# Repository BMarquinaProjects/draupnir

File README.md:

# Draupnir

Analizador lógico de 8 canales: una Raspberry Pi Pico con el firmware libre [sigrok-pico](https://github.com/pico-coder/sigrok-pico) y PulseView en el PC, sobre una PCB propia con protección de entradas. **La v1 es solo para señales de 3,3 V.** El buffer que acepta 5 V (74LVC245) llega en la v2.

**EDA:** KiCad 10, con la biblioteca Forja de [Akmon](https://github.com/BMarquinaProjects/akmon)

<!-- Foto de la placa montada: fotos/draupnir.jpg (5 dic) -->

## Especificación

| | v1 |
|---|---|
| Canales | 8: D2 a D9 de sigrok-pico (GPIO 2 a 9 de la Pico) |
| Niveles de entrada | 3,3 V. **No admite 5 V** |
| Protección por canal | Resistencia en serie de 1 kΩ (decisión 2 de la bitácora; cuentas en MEDIDAS.md) |
| Conector de entrada | 2 × 8, paso 2,54 mm, con una masa junto a cada señal |
| Muestreo máximo útil | _____ MHz (limitado por _____) |
| Firmware | sigrok-pico, versión _____ |
| Software en el PC | PulseView nightly del _____ |
| Placa | 2 capas, 58,4 × 55,9 mm, todo de agujero pasante, JLCPCB |

## La placa

| Cara superior | Cara inferior |
|---|---|
|  |  |

Pistas por la cara de arriba y plano de masa entero por la de abajo. Los Gerbers de cada pedido están en las [releases](../../releases).

## Cómo se usa

1. Flashea sigrok-pico: mantén BOOTSEL, conecta la Pico por USB y arrastra el `.uf2`.
2. Abre PulseView (versión nightly: la 0.4.2 no reconoce sigrok-pico) y elige el controlador de la Pico y su puerto COM.
3. **Une primero las masas** de Draupnir y del circuito que vas a medir.
4. Conecta las señales a los pines pares de J1, rotulados D2 a D9 como en PulseView. Solo de 3,3 V: la resistencia en serie no protege de los 5 V.
5. Elige una frecuencia de muestreo de al menos 10 veces la de la señal y añade el decodificador (UART, I²C o SPI).

## Medidas

Resumen de [MEDIDAS.md](MEDIDAS.md). _Se rellena al cerrar la campaña._

## Cómo fabricarla

Para quien no tenga la herramienta del diseño: el esquema en PDF está en `docs/draupnir-esquema.pdf` y los Gerbers de cada pedido, en las releases del repositorio. La BOM está en `hardware/fabricacion/`.

## Lo que aprendí

- El flujo entero de una placa: biblioteca, esquema, layout, DRC y Gerbers.
- Proteger entradas: qué limita una resistencia en serie y qué no.
- Niveles lógicos, y por qué un 74LVC alimentado a 3,3 V acepta 5 V en sus entradas (v2).
- Muestreo: frecuencia, Nyquist y profundidad de memoria.
- Decodificar UART, I²C y SPI de mis propios montajes.

## Bitácora

[BITACORA.md](BITACORA.md)

## Ficha del proyecto

[ficha.html](ficha.html): especificación, decisiones de diseño, capturas y medidas en una página.

## Licencia

Por decidir antes de pasar a Hierro.

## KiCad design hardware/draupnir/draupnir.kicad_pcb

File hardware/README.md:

# hardware

Aquí va el proyecto de Draupnir. Se crea en el paso 0.2 de la guía, con el nombre `draupnir` y dentro de esta carpeta. Hay una guía por herramienta, `guia-kicad.html` y `guia-altium.html`: se elige una y no se cambia a mitad.

| Si es en KiCad 10 | Si es en Altium Designer 26 | Qué es |
|---|---|---|
| `draupnir\draupnir.kicad_pro` | `Draupnir\Draupnir.PrjPcb` | El proyecto |
| `draupnir\draupnir.kicad_sch` | `Draupnir\Draupnir.SchDoc` | El esquema |
| `draupnir\draupnir.kicad_pcb` | `Draupnir\Draupnir.PcbDoc` | La placa |
| `fabricacion\gerbers\` | `Draupnir\Project Outputs for Draupnir\` | Donde la herramienta escribe los Gerbers y los taladros. Git lo ignora |

En las dos:

| Archivo | Qué es |
|---|---|
| `fabricacion\draupnir-v1.0-gerbers.zip` | Lo que se envía a JLCPCB. Git lo ignora; se publica como release |
| `fabricacion\draupnir-v1.0-bom.csv` | La lista de piezas. Sí va a git |

- Las piezas propias no están aquí: salen de Akmon. En KiCad, de `FORJA\akmon\biblioteca\forja.pretty`; en Altium, de `FORJA\akmon\altium\Forja.SchLib` y `Forja.PcbLib`. El esquema y la placa guardan una copia de cada pieza, así que el proyecto se abre aunque falte Akmon.
- Cada pedido se etiqueta en git (`v1.0`, `v1.1`…) y se publica como release con su zip.

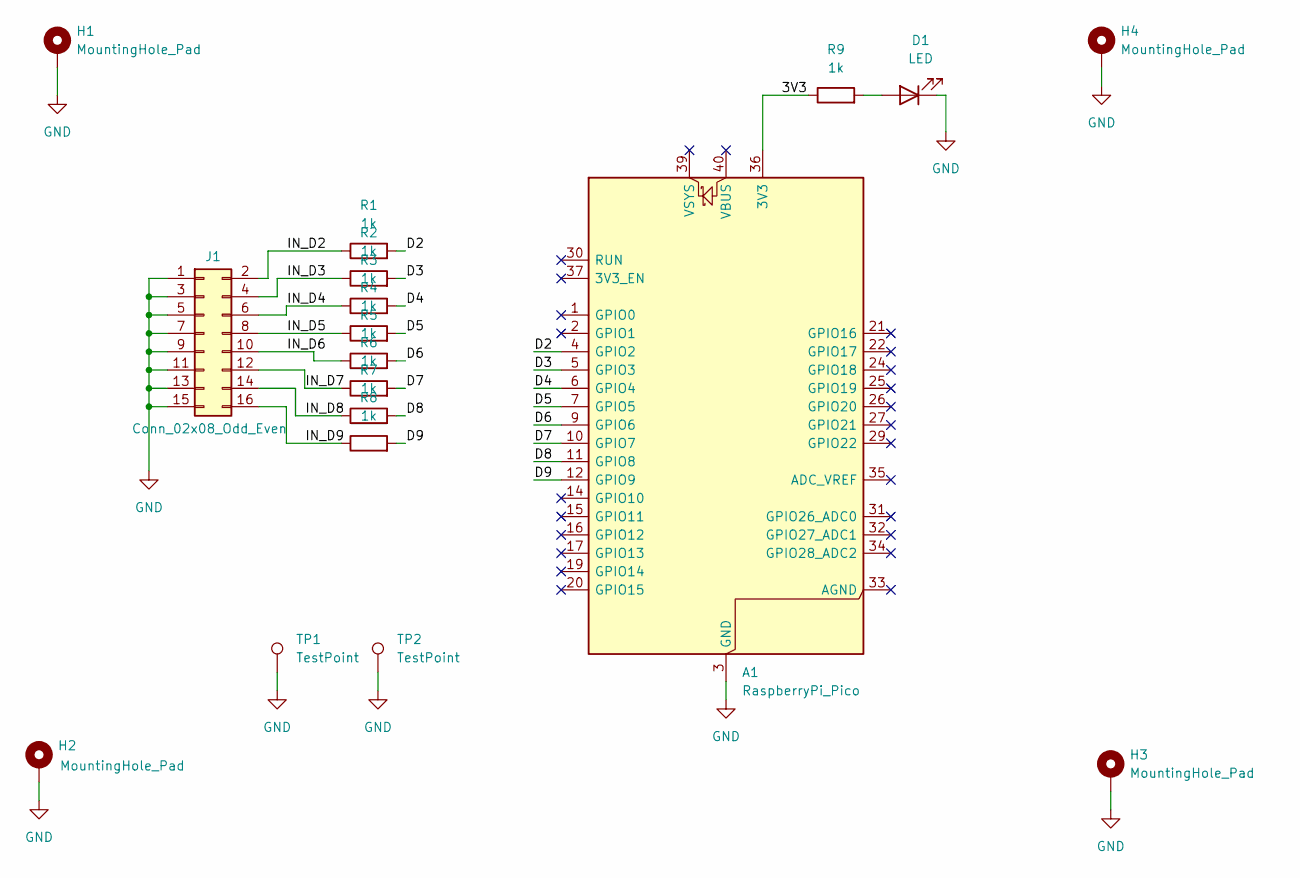
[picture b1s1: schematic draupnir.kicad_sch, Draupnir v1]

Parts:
A1: RaspberryPi_Pico; RaspberryPi_Pico_Common_THT
D1: LED; LED_D3.0mm
H1, H2, H3, H4: MountingHole_Pad; MountingHole_3.2mm_M3_Pad
J1: Conn_02x08_Odd_Even; PinHeader_2x08_P2.54mm_Vertical
R1, R2, R3, R4, R5, R6, R7, R8, R9: 1k; R_Axial_DIN0207_L6.3mm_D2.5mm_P10.16mm_Compacta
TP1, TP2: TestPoint; TestPoint_THTPad_D2.0mm_Drill1.0mm

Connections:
/3V3: A1.36 (3V3), R9.1
/D2: A1.4 (GPIO2), R1.2
/D3: A1.5 (GPIO3), R2.2
/D4: A1.6 (GPIO4), R3.2
/D5: A1.7 (GPIO5), R4.2
/D6: A1.9 (GPIO6), R5.2
/D7: A1.10 (GPIO7), R6.2
/D8: A1.11 (GPIO8), R7.2
/D9: A1.12 (GPIO9), R8.2
/IN_D2: J1.2, R1.1
/IN_D3: J1.4, R2.1
/IN_D4: J1.6, R3.1
/IN_D5: J1.8, R4.1
/IN_D6: J1.10, R5.1
/IN_D7: J1.12, R6.1
/IN_D8: J1.14, R7.1
/IN_D9: J1.16, R8.1
GND: A1.3 (GND), A1.8 (GND), A1.13 (GND), A1.18 (GND), A1.23 (GND), A1.28 (GND), A1.38 (GND), D1.1 (K), H1.1 (1_1), H2.1 (1_1), H3.1 (1_1), H4.1 (1_1), J1.1, J1.3, J1.5, J1.7, J1.9, J1.11, J1.13, J1.15, TP1.1 (1_1), TP2.1 (1_1)
unnamed: D1.2 (A), R9.2

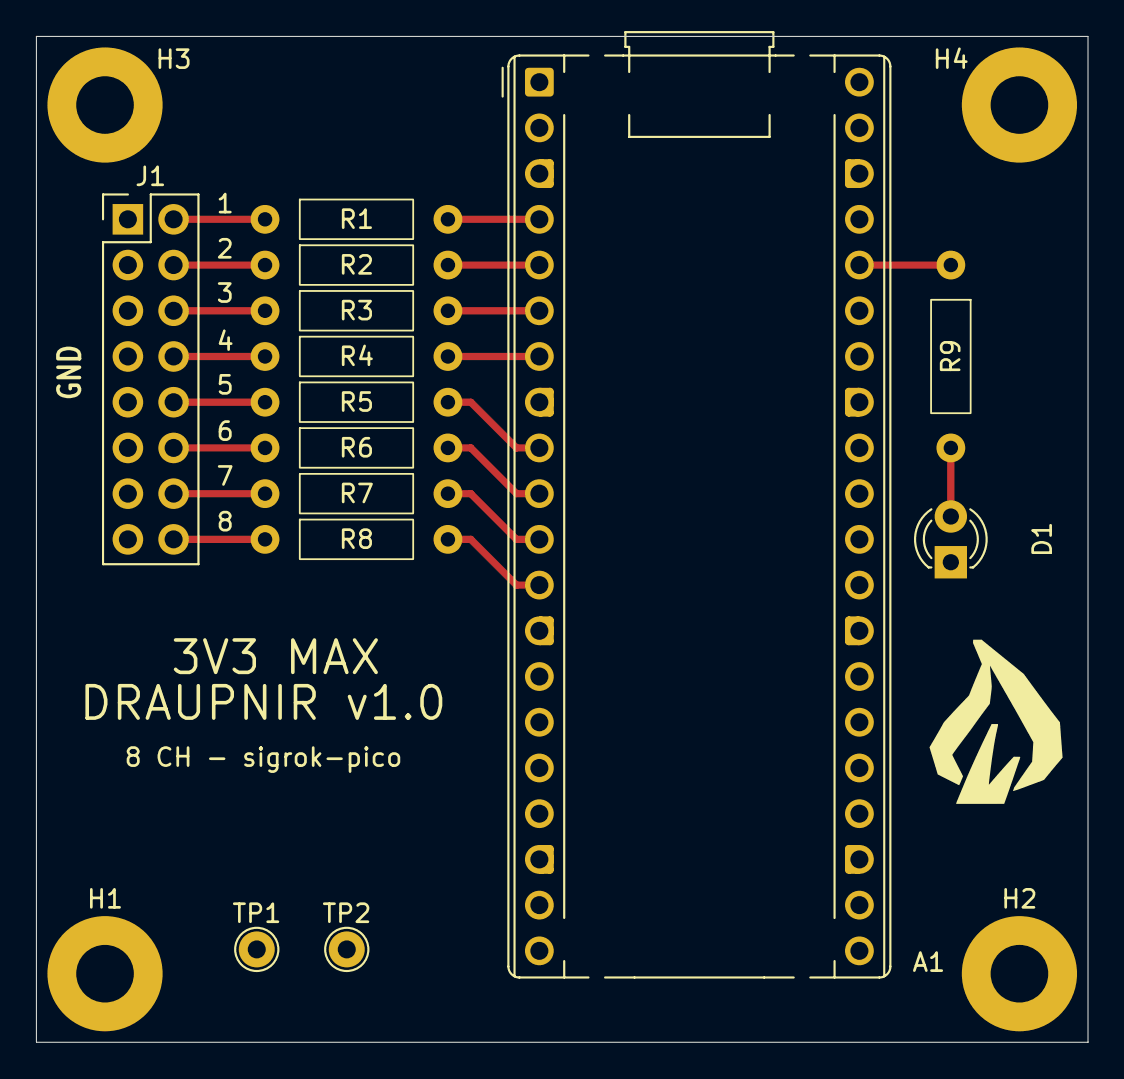
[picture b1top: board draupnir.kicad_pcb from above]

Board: 2 copper layers, 58.4 x 55.9 mm, 18 parts (0 on the bottom side), 19 nets.
